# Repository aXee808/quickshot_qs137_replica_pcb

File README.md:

# quickshot\_qs137\_replica\_pcb

Quickshot QS137 db9 joystick replica PCB prototype (kicad gerber file)

## Images

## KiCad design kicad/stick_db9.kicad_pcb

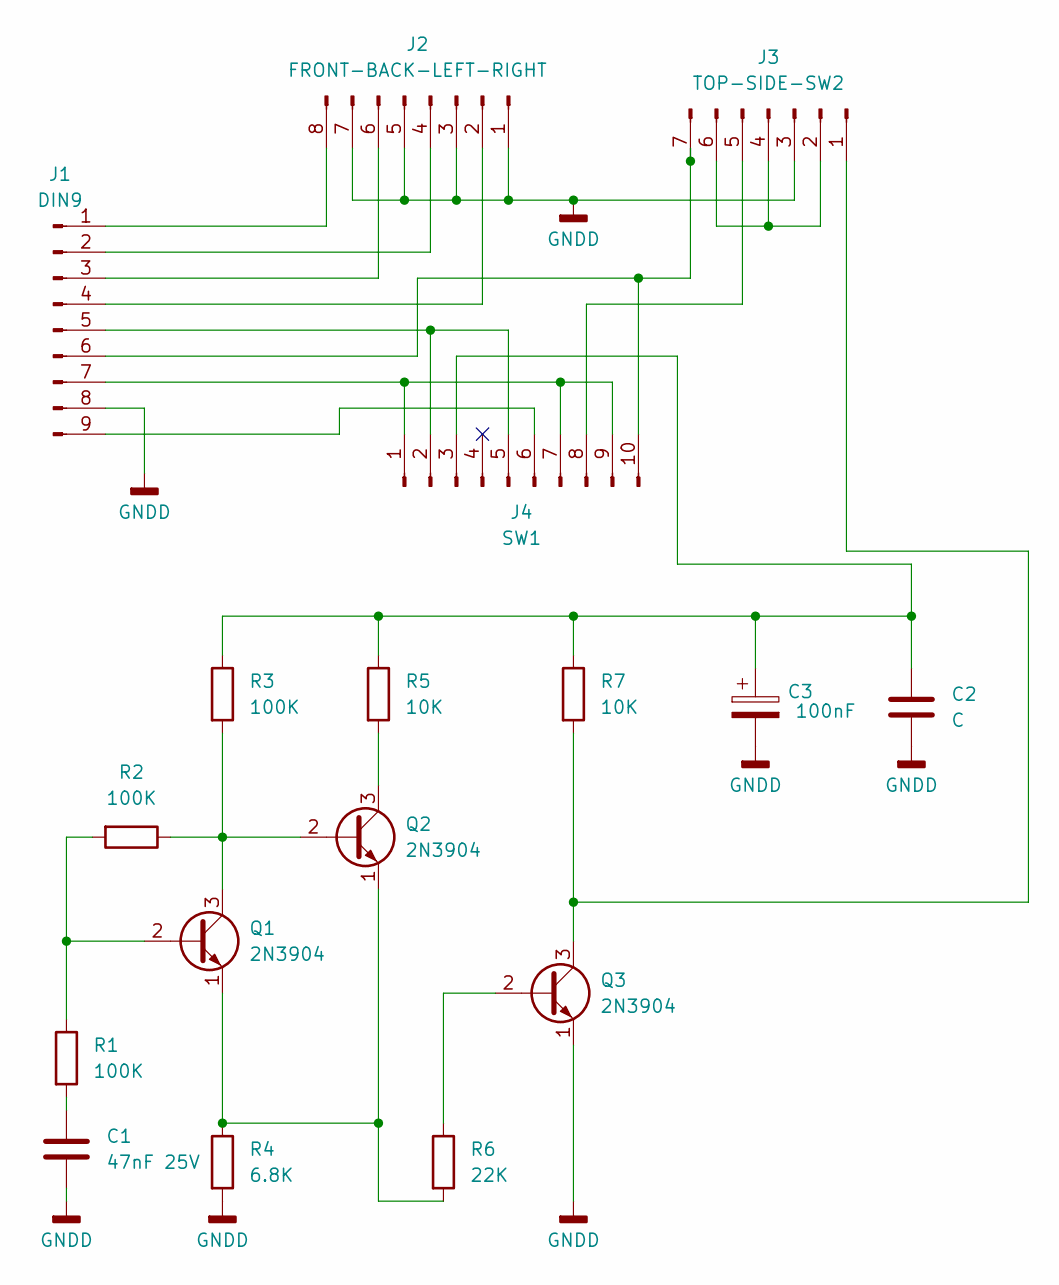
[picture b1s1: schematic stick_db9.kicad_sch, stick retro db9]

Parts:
C1: 47nF 25V; CP_Axial_L10.0mm_D4.5mm_P15.00mm_Horizontal
C2: C; CP_Radial_D5.0mm_P2.00mm
C3: 100nF; CP_Radial_D5.0mm_P2.00mm
J1: DIN9; PinHeader_1x09_P1.00mm_Vertical
J2: FRONT-BACK-LEFT-RIGHT; PinHeader_1x08_P1.00mm_Vertical
J3: TOP-SIDE-SW2; PinHeader_1x07_P1.00mm_Vertical
J4: SW1; PinHeader_1x10_P1.00mm_Vertical
Q1, Q2, Q3: 2N3904; TO-92_Inline
R1, R2, R3: 100K; R_Axial_DIN0207_L6.3mm_D2.5mm_P10.16mm_Horizontal
R4: 6.8K; R_Axial_DIN0207_L6.3mm_D2.5mm_P10.16mm_Horizontal
R5, R7: 10K; R_Axial_DIN0207_L6.3mm_D2.5mm_P10.16mm_Horizontal
R6: 22K; R_Axial_DIN0207_L6.3mm_D2.5mm_P10.16mm_Horizontal

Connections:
GNDD: C1.2, C2.2, C3.2, J1.8, J2.1, J2.3, J2.5, J2.7, J3.3, Q3.1 (E), R4.2
unnamed: C1.1, R1.2
unnamed: J1.1, J2.8
unnamed: J1.2, J2.4
unnamed: J1.3, J2.6
unnamed: J1.4, J2.2
unnamed: J1.5, J4.2, J4.5
unnamed: J1.6, J3.7, J4.10
unnamed: J1.7, J4.1, J4.7, J4.9
unnamed: J1.9, J4.6
unnamed: J3.1, Q3.3 (C), R7.2
unnamed: J3.2, J3.4, J3.6
unnamed: J3.5, J4.8
unnamed: C2.1, C3.1, J4.3, R3.1, R5.1, R7.1
unnamed: Q1.2 (B), R1.1, R2.2
unnamed: Q1.3 (C), Q2.2 (B), R2.1, R3.2
unnamed: Q1.1 (E), Q2.1 (E), R4.1, R6.2
unnamed: Q2.3 (C), R5.2
unnamed: Q3.2 (B), R6.1

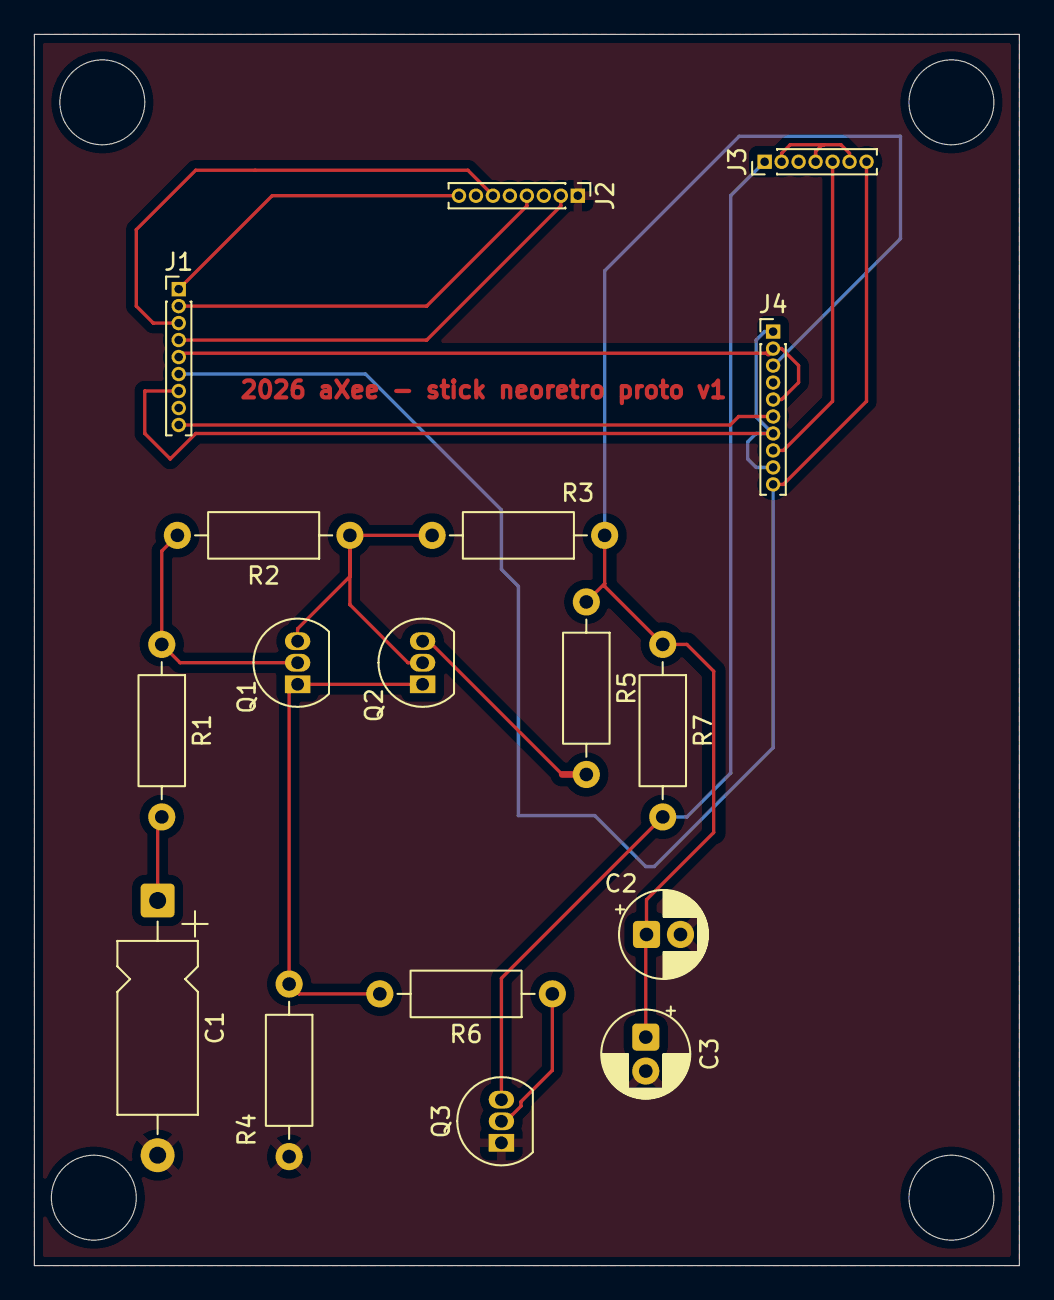
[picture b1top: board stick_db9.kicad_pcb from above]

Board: 2 copper layers, 58.0 x 72.5 mm, 17 parts (0 on the bottom side), 19 nets.

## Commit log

2026-04-08 prototype v1
